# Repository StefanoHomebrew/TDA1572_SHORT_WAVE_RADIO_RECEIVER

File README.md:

Quello che vedete è molto sperimentale, in fase di sviluppo. Non posso dare assistenza tecnica e file gerber... Se trovate BUG e avete consigli utili, scrivetemi! Grazie!  Altrimenti che divertimento è!... A very experimental shortwave radio receiver with TDA1572, a vintage integrated circuit, external PLL & DDS Vfo and Arduino Mega 256. Gennaio 2025, AM-SSB-RTTY(in fase di sviluppo)---Aprile 2025--- Nuova release con AGC NUOVO! : RX_TDA1572_AGC_NEW_REV2.kicad_pcb

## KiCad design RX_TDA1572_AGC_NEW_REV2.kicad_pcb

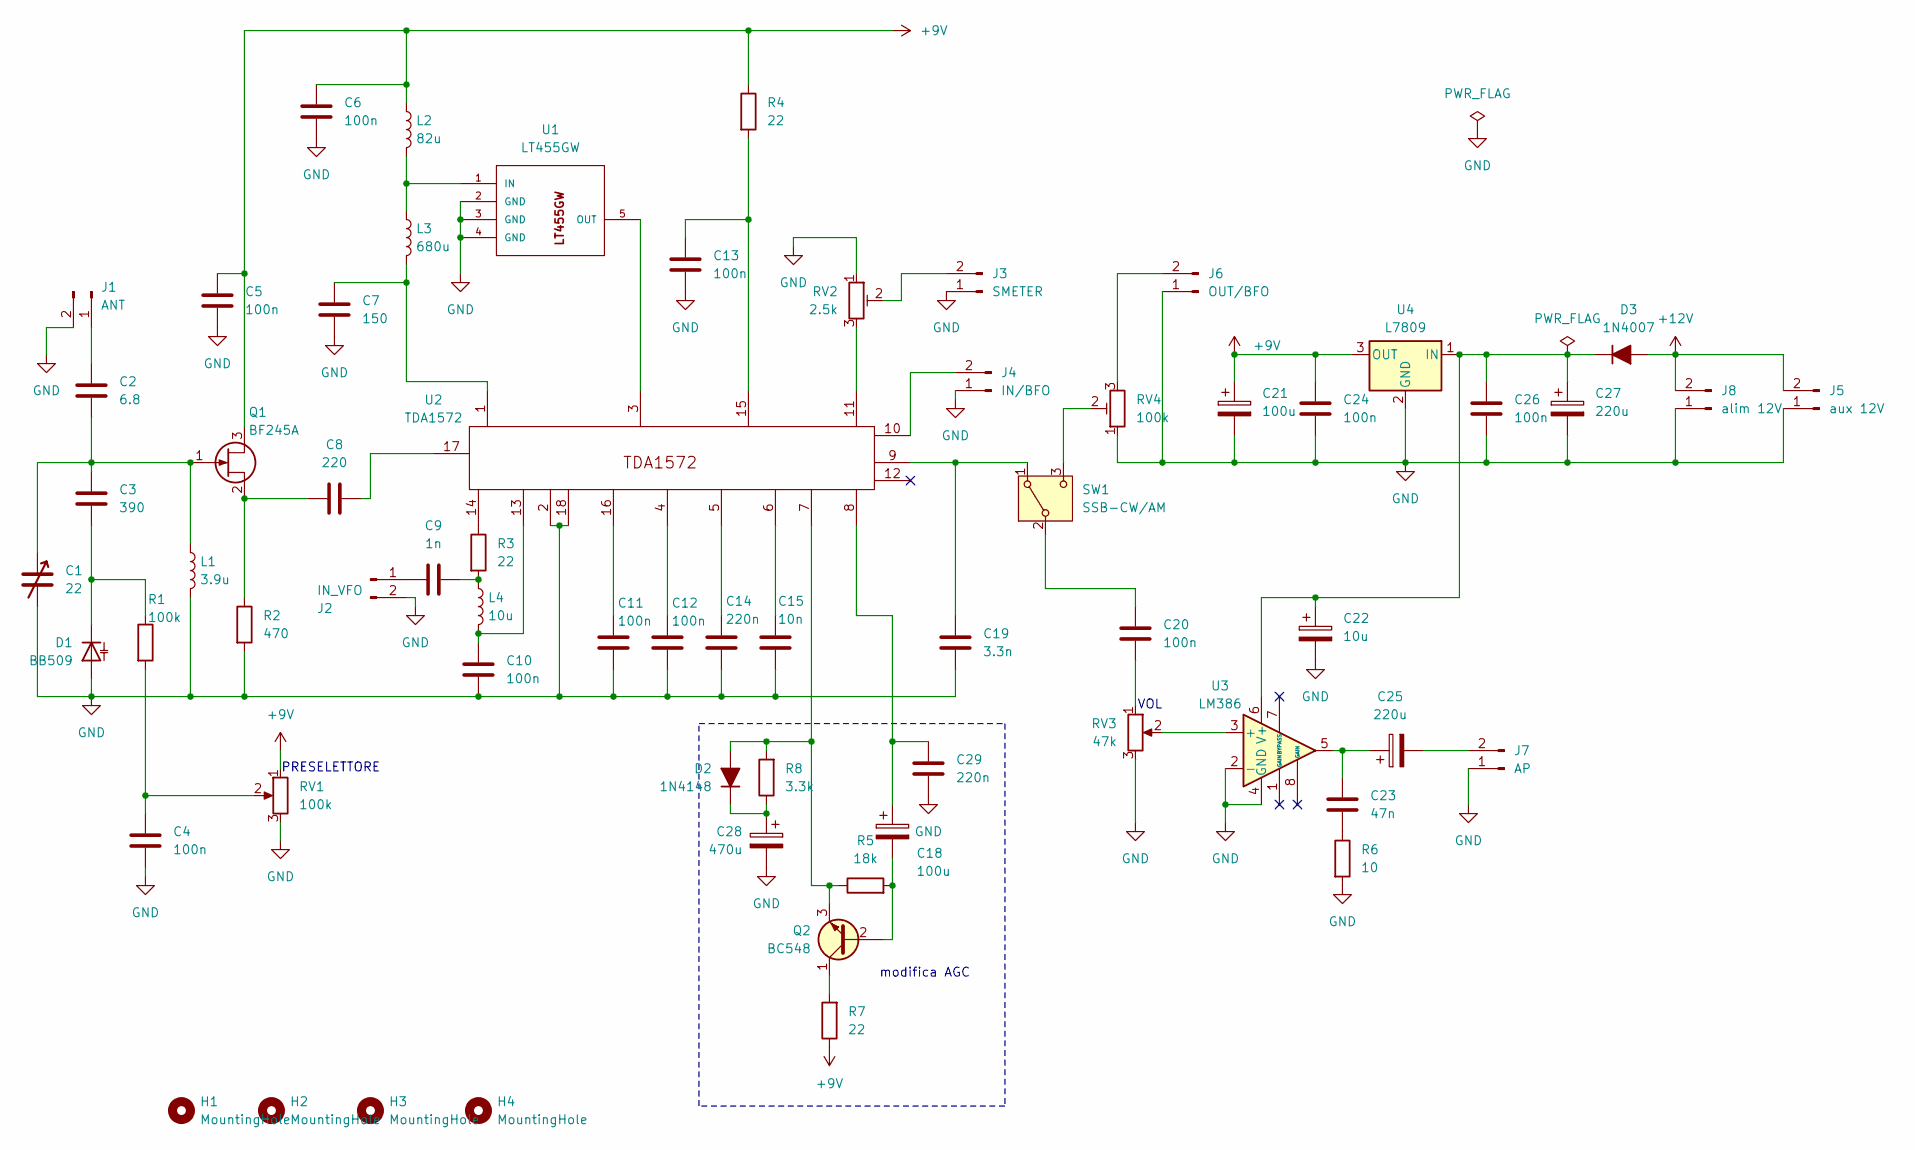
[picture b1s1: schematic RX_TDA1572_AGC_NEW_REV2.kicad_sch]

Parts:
C1: 22; C_Rect_L9.0mm_W3.4mm_P7.50mm_MKT
C2: 6.8; C_Rect_L9.0mm_W3.4mm_P7.50mm_MKT
C3: 390; C_Rect_L9.0mm_W3.4mm_P7.50mm_MKT
C4, C5, C6, C10, C11, C12, C13, C20, C24, C26: 100n; C_Rect_L9.0mm_W3.4mm_P7.50mm_MKT
C7: 150; C_Rect_L9.0mm_W3.4mm_P7.50mm_MKT
C8: 220; C_Rect_L9.0mm_W3.4mm_P7.50mm_MKT
C9: 1n; C_Rect_L9.0mm_W3.4mm_P7.50mm_MKT
C14, C29: 220n; C_Rect_L9.0mm_W3.4mm_P7.50mm_MKT
C15: 10n; C_Rect_L9.0mm_W3.4mm_P7.50mm_MKT
C18, C21: 100u; CP_Radial_D8.0mm_P5.00mm
C19: 3.3n; C_Rect_L9.0mm_W3.4mm_P7.50mm_MKT
C22: 10u; CP_Radial_D5.0mm_P2.50mm
C23: 47n; C_Rect_L9.0mm_W3.4mm_P7.50mm_MKT
C25, C27: 220u; CP_Radial_D8.0mm_P5.00mm
C28: 470u; CP_Radial_D8.0mm_P5.00mm
D1: BB509; D_A-405_P7.62mm_Horizontal
D2: 1N4148; D_DO-35_SOD27_P7.62mm_Horizontal
D3: 1N4007; D_DO-41_SOD81_P7.62mm_Horizontal
H1, H2, H3, H4: MountingHole; MountingHole_2.5mm_Pad
J1: ANT; PinHeader_1x02_P2.54mm_Vertical
J2: IN_VFO; PinHeader_1x02_P2.54mm_Vertical
J3: SMETER; PinHeader_1x02_P2.54mm_Vertical
J4: IN/BFO; PinHeader_1x02_P2.54mm_Vertical
J5: aux 12V; PinHeader_1x02_P2.54mm_Vertical
J6: OUT/BFO; PinHeader_1x02_P2.54mm_Vertical
J7: AP; PinHeader_1x02_P2.54mm_Vertical
J8: alim 12V; PinHeader_1x02_P2.54mm_Vertical
L1: 3.9u; L_Axial_L7.0mm_D3.3mm_P12.70mm_Horizontal_Fastron_MICC
L2: 82u; L_Axial_L7.0mm_D3.3mm_P12.70mm_Horizontal_Fastron_MICC
L3: 680u; L_Axial_L7.0mm_D3.3mm_P12.70mm_Horizontal_Fastron_MICC
L4: 10u; L_Axial_L7.0mm_D3.3mm_P12.70mm_Horizontal_Fastron_MICC
Q1: BF245A; TO-92_Inline_Wide
Q2: BC548; TO-92_Inline_Wide_CBE
R1: 100k; R_Axial_DIN0207_L6.3mm_D2.5mm_P10.16mm_Horizontal
R2: 470; R_Axial_DIN0207_L6.3mm_D2.5mm_P10.16mm_Horizontal
R3, R4, R7: 22; R_Axial_DIN0207_L6.3mm_D2.5mm_P10.16mm_Horizontal
R5: 18k; R_Axial_DIN0207_L6.3mm_D2.5mm_P10.16mm_Horizontal
R6: 10; R_Axial_DIN0207_L6.3mm_D2.5mm_P10.16mm_Horizontal
R8: 3.3k; R_Axial_DIN0207_L6.3mm_D2.5mm_P10.16mm_Horizontal
RV1: 100k; Potentiometer_Piher_PT-15-H01_Horizontal
RV2: 2.5k; Potentiometer_Runtron_RM-065_Vertical
RV3: 47k; Potentiometer_Piher_PT-15-H01_Horizontal
RV4: 100k; Potentiometer_Runtron_RM-065_Vertical
SW1: SSB-CW/AM; PinHeader_1x03_P2.54mm_Vertical
U1: LT455GW; CFW455IT
U2: TDA1572; DIP-18_W7.62mm_Socket_LongPads
U3: LM386; DIP-8_W7.62mm_Socket_LongPads
U4: L7809; TO-220-3_Vertical

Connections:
+9V: C5.1, C6.1, C21.1, C24.1, L2.1, Q1.3 (D), R4.1, R7.1, RV1.1, U4.3 (OUT)
+12V: D3.2 (A), J5.2, J8.2
GND: C1.2, C4.2, C5.2, C6.2, C7.2, C10.1, C11.1, C12.1, C13.2, C14.1, C15.1, C19.2, C21.2, C22.2, C24.2, C26.2, C27.2, C28.2, C29.2, D1.2 (A), J1.2, J2.2, J3.1, J4.1, J5.1, J6.1, J7.1, J8.1, L1.2, R2.2, R6.2, RV1.3, RV2.1, RV3.3, RV4.1, U1.2 (GND), U1.3 (GND), U1.4 (GND), U2.2, U2.18, U3.2 (-), U3.4 (GND), U4.2 (GND)
unnamed: C4.1, R1.2, RV1.2
unnamed: C7.1, L3.2, U2.1
unnamed: C8.2, U2.17
unnamed: C9.2, L4.1, R3.2
unnamed: C10.2, L4.2, U2.13
unnamed: C11.2, U2.16
unnamed: C12.2, U2.4
unnamed: C13.1, R4.2, U2.15
unnamed: C14.2, U2.5
unnamed: C15.2, U2.6
unnamed: C18.1, C29.1, U2.8
unnamed: C20.1, RV3.1
unnamed: C23.1, C25.1, U3.5
unnamed: C23.2, R6.1
unnamed: C3.2, D1.1 (K), R1.1
unnamed: D2.2 (A), Q2.3 (E), R5.1, R8.2, U2.7
unnamed: C28.1, D2.1 (K), R8.1
unnamed: C22.1, C26.1, C27.1, D3.1 (K), U3.6 (V+), U4.1 (IN)
unnamed: C2.1, J1.1
unnamed: C9.1, J2.1
unnamed: J3.2, RV2.2
unnamed: J4.2, U2.10
unnamed: J6.2, RV4.3
unnamed: C25.2, J7.2
unnamed: C1.1, C2.2, C3.1, L1.1, Q1.1 (G)
unnamed: C8.1, Q1.2 (S), R2.1
unnamed: C18.2, Q2.2 (B), R5.2
unnamed: Q2.1 (C), R7.2
unnamed: R3.1, U2.14
unnamed: RV2.3, U2.11
unnamed: C19.1, SW1.1 (A), U2.9
unnamed: C20.2, SW1.2 (B)
unnamed: RV4.2, SW1.3 (C)
unnamed: L2.2, L3.1, U1.1 (IN)
unnamed: U1.5 (OUT), U2.3
unnamed: RV3.2, U3.3 (+)

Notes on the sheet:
modifica AGC
PRESELETTORE
VOL

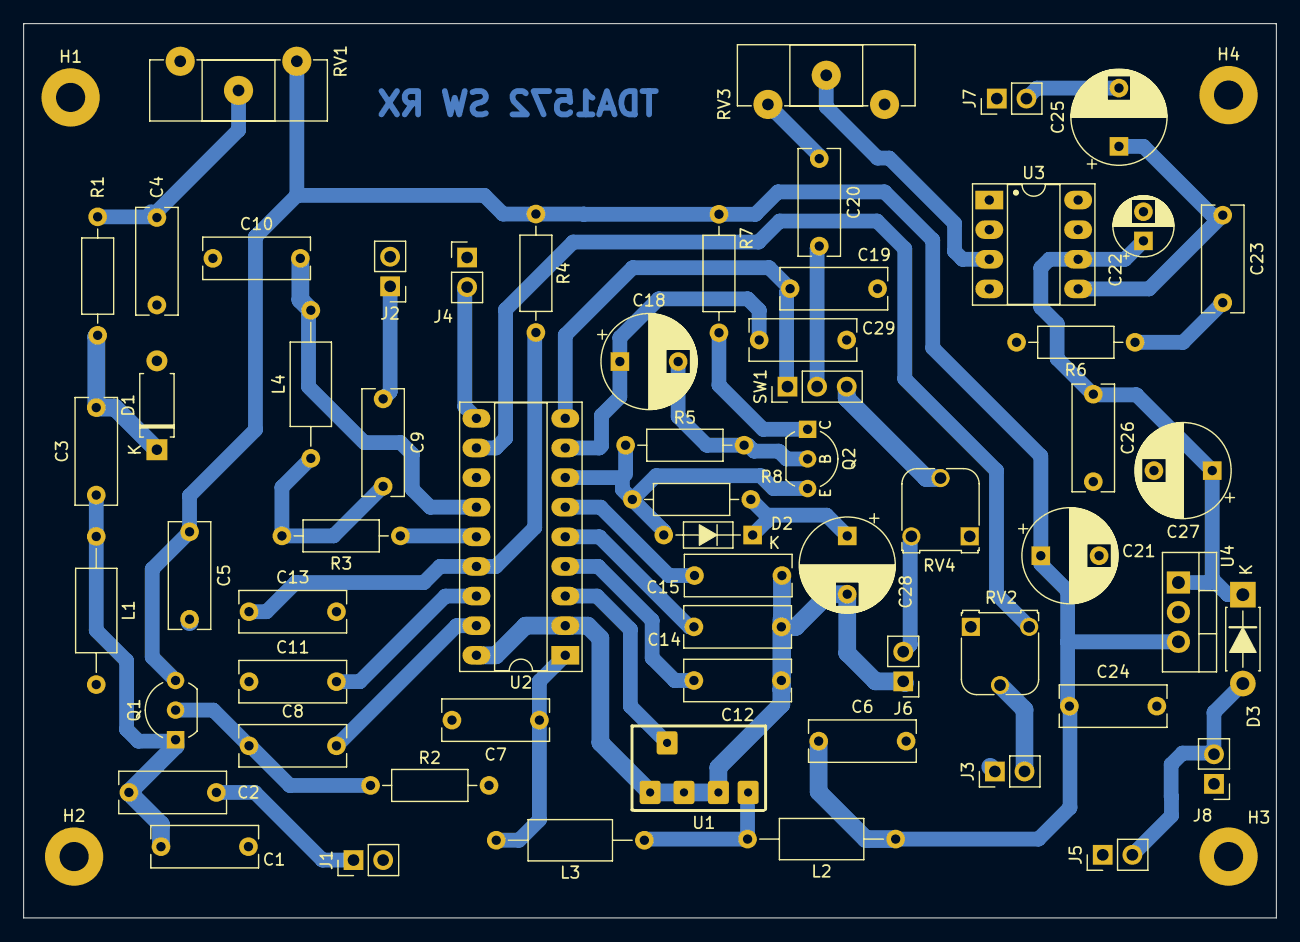
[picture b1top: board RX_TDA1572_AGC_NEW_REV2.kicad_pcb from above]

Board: 2 copper layers, 107.4 x 76.7 mm, 65 parts (0 on the bottom side), 39 nets.

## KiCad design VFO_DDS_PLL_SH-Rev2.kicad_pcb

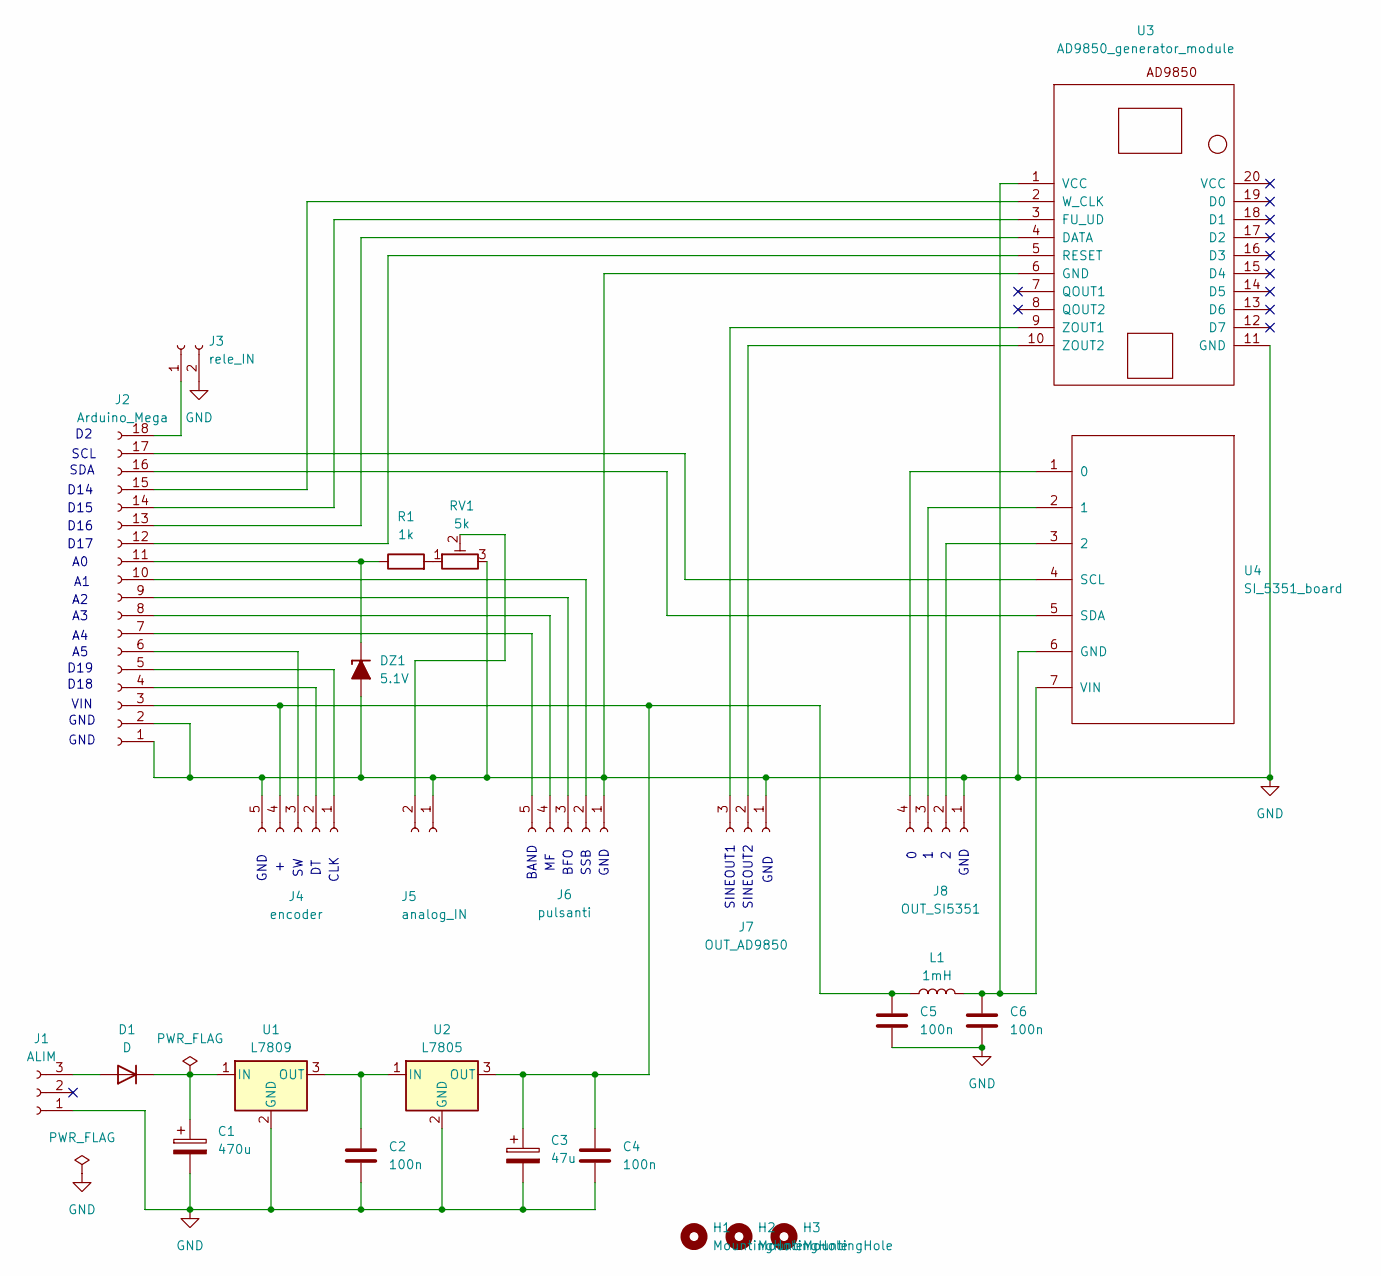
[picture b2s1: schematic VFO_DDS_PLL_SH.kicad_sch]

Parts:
C1: 470u; CP_Radial_D8.0mm_P3.50mm
C2, C4, C5, C6: 100n; C_Disc_D4.3mm_W1.9mm_P5.00mm
C3: 47u; CP_Radial_D8.0mm_P3.50mm
D1: D; D_DO-41_SOD81_P12.70mm_Horizontal
DZ1: 5.1V; D_DO-34_SOD68_P7.62mm_Horizontal_Zener
H1, H2, H3: MountingHole; MountingHole_2.2mm_M2_Pad
J1: ALIM; PinHeader_1x03_P2.54mm_Vertical
J2: Arduino_Mega; PinHeader_1x18_P2.54mm_Vertical
J3: rele_IN; PinHeader_1x02_P2.54mm_Vertical
J4: encoder; PinHeader_1x05_P2.54mm_Vertical
J5: analog_IN; PinHeader_1x02_P2.54mm_Vertical
J6: pulsanti; PinHeader_1x05_P2.54mm_Vertical
J7: OUT_AD9850; PinHeader_1x03_P2.54mm_Vertical
J8: OUT_SI5351; PinHeader_1x04_P2.54mm_Vertical
L1: 1mH; L_Axial_L5.3mm_D2.2mm_P10.16mm_Horizontal_Vishay_IM-1
R1: 1k; R_Axial_DIN0207_L6.3mm_D2.5mm_P10.16mm_Horizontal
RV1: 5k; Potentiometer_Runtron_RM-065_Vertical
U1: L7809; TO-220-3_Horizontal_TabDown
U2: L7805; TO-220-3_Horizontal_TabDown
U3: AD9850_generator_module; AD9850-MODUL
U4: SI_5351_board; SI5351_MODULE

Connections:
GND: C1.2, C2.2, C3.2, C4.2, C5.2, C6.2, DZ1.2 (A), J1.1, J2.1, J2.2, J3.2, J4.5, J5.1, J6.1, J7.1, J8.1, RV1.3, U1.2 (GND), U2.2 (GND), U3.6 (GND), U3.11 (GND), U4.6 (GND)
unnamed: D1.2 (A), J1.3
unnamed: C1.1, D1.1 (K), U1.1 (IN)
unnamed: DZ1.1 (K), J2.11, R1.1
unnamed: C3.1, C4.1, C5.1, J2.3, J4.4, L1.1, U2.3 (OUT)
unnamed: J2.4, J4.2
unnamed: J2.5, J4.1
unnamed: J2.6, J4.3
unnamed: J2.7, J6.5
unnamed: J2.8, J6.4
unnamed: J2.9, J6.3
unnamed: J2.10, J6.2
unnamed: J2.12, U3.5 (RESET)
unnamed: J2.13, U3.4 (DATA)
unnamed: J2.14, U3.3 (FU_UD)
unnamed: J2.15, U3.2 (W_CLK)
unnamed: J2.16, U4.5 (SDA)
unnamed: J2.17, U4.4 (SCL)
unnamed: J2.18, J3.1
unnamed: J5.2, RV1.2
unnamed: J7.2, U3.10 (ZOUT2)
unnamed: J7.3, U3.9 (ZOUT1)
unnamed: J8.2, U4.3 (2)
unnamed: J8.3, U4.2 (1)
unnamed: J8.4, U4.1 (0)
unnamed: R1.2, RV1.1
unnamed: C2.1, U1.3 (OUT), U2.1 (IN)
unnamed: C6.1, L1.2, U3.1 (VCC), U4.7 (VIN)

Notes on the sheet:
BAND
SINEOUT2
SDA
GND
D18
SCL
VIN
CLK
SINEOUT1
SSB
BFO
D17
D15
D14
D16
D19

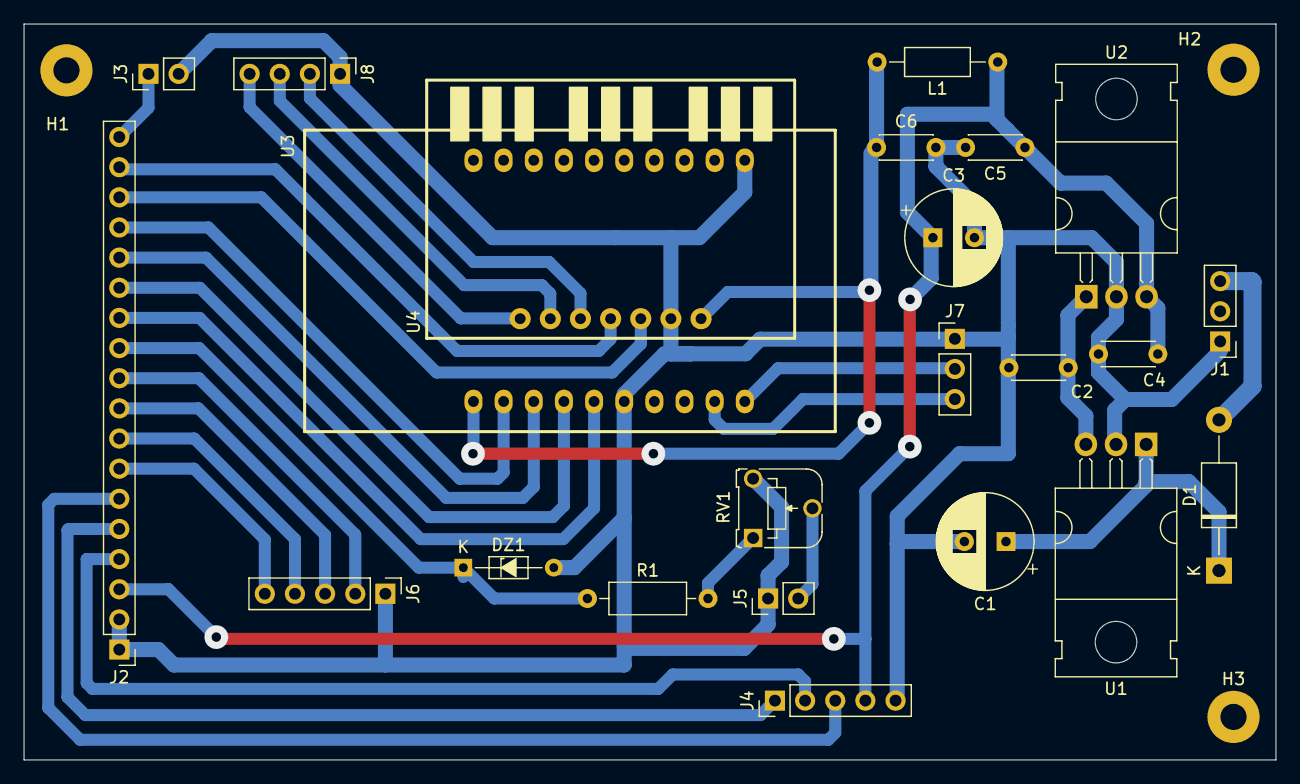
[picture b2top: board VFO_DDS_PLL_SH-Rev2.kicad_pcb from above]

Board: 2 copper layers, 105.5 x 62.0 mm, 26 parts (0 on the bottom side), 28 nets.

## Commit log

2024-12-09 Add files via upload
    A very versatile and easy to build shortwave radio receiver.
2025-01-06 Add files via upload
    File .HEX per Arduino Mega 2560 Ricevitore per Onde Corte con TDA1572 - AM -SSB - RTTY (in fase di sviluppo)
2025-01-20 ERRATA CORRIGE----Rev.2
2025-04-07 Nuova Versione AGC NEW
2025-05-10 SCHEMA ELETTRICO VFO DDS
